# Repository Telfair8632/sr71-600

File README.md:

# SR71-600 — A Twin-Engine 600 mm RC Blackbird

A fully independent engineering project: the complete digital build package, firmware, and verification records for a twin-engine radio-controlled aircraft modeled on the SR-71.

> As a fully independent engineering project, I am designing and building a twin-engine radio-controlled aircraft modeled on the SR-71, with a 590 mm airframe and a 190.7 g mass budget. I completed the full digital design phase myself: a parametric CAD model, an engineering report with assembly documentation, full-scale manufacturing templates, a costed procurement plan, and automated design-verification checks. I then established a staged verification program for the flight controller, a Raspberry Pi Pico 2 microcontroller, progressing through fourteen defined debug levels. My level-three firmware—heartbeat indication, USB logging, and watchdog recovery—passed a 30-minute automated endurance test, and my level-four inertial-measurement firmware validated the MPU-6050 sensor, logging 200 Hz data for ten continuous minutes without a dropped sample. Next, I will construct motor mounts and a thrust-test bench, calibrate weight and balance, and complete ground checks before a supervised first flight. This project demonstrates my capacity for self-directed learning, systematic execution, and safety-conscious engineering practice.

**This repository is the V1.0-P0 digital trial-production release. It is not a flight-certified design.**

## Status Snapshot

| Area | State | Evidence |
|---|---|---|
| Parametric CAD model | Done (P0) | `cad/`, `qa/cad_checks.json` |
| Engineering report & assembly manual | Done | `docs/engineering_report.md` / `.pdf` |
| Manufacturing templates (14 laser-cut DXF, 8 printed STL, 1:1 print sheets) | Done | `cut/`, `print/`, `docs/cutting_templates_1to1.pdf` |
| Circuit design (E1) | Done | `docs/circuit_design.md`, `electronics/` |
| Firmware level 3 — minimal firmware, 30-min soak + watchdog | **PASS** (2026-10-07) | `data/test_records.csv` row PICO0, `firmware/scripts/soak_level3_*.log` |
| Firmware level 4 — MPU-6050 IMU @ 200 Hz, 10-min log | **PASS** (2026-10-13); accelerometer scale error corrected in firmware 2026-11-19 | `data/test_records.csv` row IMU0, `firmware/scripts/imu_10min.csv`, `docs/debug_log_2026-11-19.md` |
| Firmware level 6 — four-channel 50 Hz PWM | Compiled (2026-10-19), artifact verified reproducible; flash + logic-analyser verification pending | `firmware/level6_pwm/`, `docs/debug_log_2026-10-19.md` |
| E1 power-distribution PCB (V1.1) | **Received 2026-11-19, bare board verified by continuity**, assembly pending (3 parts still missing) | `pcb/e1_power_dist_2s/`, `docs/pcb_v1_1_wiring.md` |
| SMD flight-control board V2 | **Designed 2026-11-19**: 65 × 85 mm, 37 SMD parts, routed, DRC 0/0; ordering pending | `pcb/sr71_ctrl_v2/`, `docs/pcb_v2_smd_design.md` |
| Physical build & flight test | In progress — V1.1 becomes the bench board; the V2 SMD board is the flight-intent board | `docs/debug_log_2026-11-19.md`, `ROADMAP.md` |

## Repository Layout

```
cad/                FreeCAD source model (.FCStd) and STEP export
config/             design.json — the parametric design entry point
cut/                14 laser-cutting DXF templates (foam sheets)
print/              8 3D-printed parts (motor saddles, fin saddles, control horns)
docs/               engineering report, assembly instructions, circuit design,
                    staged debug procedure, debug logs, assessments, learning path
electronics/        wiring diagram (SVG) and netlist (CSV), revision E1
pcb/                two boards: e1_power_dist_2s (V1.1, through-hole, received) and
                    sr71_ctrl_v2 (V2, SMD, 65 x 85 mm) — KiCad sources, Gerbers,
                    CPL, BOM, renders
firmware/           Pico 2 (RP2350) firmware: level3_minimal, level4_imu, level6_pwm,
                    bus_doctor, plus the automated acceptance scripts and raw test logs
data/               BOM, procurement budget, test records, measurement records,
                    analysis outputs (JSON) consumed by the generators
src/                Python generators that build the CAD, drawings, PDFs, DXFs,
                    and the offline 3D viewer from config/design.json
qa/                 recorded verification evidence (CAD checks, document checks,
                    viewer checks, run logs)
references/         source links for the reference documents used during design
ROADMAP.md          phase plan, firmware ladder status, next actions, v2 gate
build.ps1           one-command regeneration of the digital package
```

Start here:

- Open `model_preview.html` in a browser — an offline interactive 3D view (drag to rotate; top/side/internal views).
- Read `docs/engineering_report.md` — design, calculations, assembly, wiring, testing, and budget.
- `docs/assembly_dimensions.pdf` and `docs/cutting_templates_1to1.pdf` — dimensioned drawings and 1:1 print templates.
- `docs/debug_procedure.md` — the 14-level staged verification program.
- `docs/debug_log_2026-10-13.md`, `docs/debug_log_2026-10-19.md`, and `docs/log_2026-10-21_e1_pcb.md` — troubleshooting retrospective, board bring-up log, and the PCB design/order log.

## Design Baseline

- Envelope 590 mm long (including propeller thickness), 420 mm span, 190 mm motor axis spacing; belly landing.
- Two micro brushless motors (EX1103 KV11000) driving 2-inch normal/reverse propellers on a 2S battery.
- Mass budget 190.7 g, including a 20 g unallocated reserve and 16 g removable steel ballast; final ballast is set by measured CG.
- First-order CG window from the full chine projection: 292.2–298.6 mm from the nose (not an aerodynamically validated result).
- First-round procurement budget CNY 3420 with CNY 1580 held back for rework and spares; not live pricing.

## Reproducing the Build

Requirements: [FreeCAD 1.1.3](https://www.freecad.org) (its bundled Python 3.11) and a Python 3.12 with `ezdxf`, `shapely`, `reportlab`, `pymupdf` (or a `tools/pydeps` folder next to this repo, which the scripts pick up automatically).

```powershell
powershell -ExecutionPolicy Bypass -File build.ps1
```

The design entry points are `config/design.json` and `src/build_cad.py`. The FCStd spreadsheet is a readable parameter list; not every solid is driven by it in real time. The scripts contain explicit modeling stations — if you change overall proportions, revise them together and re-run all checks. STLs are at local origins; STEP/FCStd use whole-aircraft coordinates. Equipment in the CAD is envelope geometry; the appearance prototype is not a strict scale replica.

Rebuilds preserve the measured columns in `data/bom.csv` and all user records in `data/test_records.csv`.

Firmware rebuild instructions (Pico SDK toolchain): see `firmware/README.md`.

## Safety and Limitations

- This is a **digital trial-production release**: hole positions and flight parameters are not measured-and-released values.
- Blank test records must never be treated as passed; propeller-disc geometry is illustrative, not a manufacturable propeller.
- The parachute bay is reserved space only — there is no parachute recovery system.
- Propellers stay off for debug levels 0–7; powered tests only on a fixed bench, never with people in the propeller plane.
- First flights are conducted by an experienced pilot, at a field with confirmed permission, clearance, and people segregation.

## License

MIT — see `LICENSE`. Third-party reference documents (receiver and motor manuals) used during design are not redistributed in this repository; see `references/sources.json` for their origins.

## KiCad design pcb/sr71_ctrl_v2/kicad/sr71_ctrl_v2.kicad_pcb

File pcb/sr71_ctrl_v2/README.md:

# SR71-600 Flight-Control Board V2 (SMD)

Board: 65 × 85 mm, 2 layers, 1.0 mm, 1 oz copper, 37 SMD parts + 4 × M2 mounting holes.
Designed 2026-11-19; DRC clean (0 violations / 0 unconnected); **not yet ordered**.
Revision 2026-11-20: the four board-outline corner arcs had the wrong sweep direction; fixed in the board file and the fabrication package re-exported.

This board replaces the through-hole `pcb/e1_power_dist_2s/` board as the flight-intent control board. The battery / ESC / UBEC distribution moved off the board, so the board now starts at 5 V and can be assembled by a PCB house in one pass.

- Electrical design and rationale: `docs/pcb_v2_smd_design.md`
- Wiring of the previous board (for reference): `docs/pcb_v1_1_wiring.md`
- Design log: `docs/debug_log_2026-11-19.md`

## Contents

```
kicad/sr71_ctrl_v2.kicad_pcb    routed board (KiCad 10)
kicad/sr71_ctrl_v2.kicad_sch    schematic
kicad/sr71_ctrl_v2.net          netlist
fab/gerbers/                    Gerber + Excellon drill set
fab/assembly/bom_sr71_ctrl_v2.csv        37-line BOM (R17/R18 = DNP)
fab/assembly/sr71_ctrl_v2_positions.csv  pick-and-place (KiCad coordinates, Y negative)
renders/board_preview.png       copper preview (top)
renders/refs_map.png            reference designator map
```

## Fabrication

| Option | Value |
|---|---|
| Layers / thickness / copper | 2 / **1.0 mm** / **1 oz** |
| Surface / mask / silk | HASL / green / white |
| Quantity | 5 |
| Assembly | single-side SMT, 5 boards |
| Not placed | R17, R18 (DNP); J5 XT30 (through-hole, hand-solder 2 pads) |

Estimated cost: CNY 150–250 for five assembled boards, 3–6 days.

## Electrical summary

Same netlist as E1 minus the power section (25 nets):

- J5 = 5 V input (XT30; pin 4 = +5 V, pin 3 = GND) — the only hand-soldered joint
- J6/J7 = servo L/R (signal, +5 V, GND); J8/J9 = ESC signal L/R
- J10 = RP1 receiver (5 V, GND, TX → U2 → GP1, RX ← R1 ← GP0)
- J11 = MPU-6050 (3V3, GND, SDA, SCL, INT) — note the SDA/SCL cross against the GY-521 header
- J12/J13 = Pico 2 sockets (SMD, 2 × 20 pins)
- U1 = SN74AHCT125 (SOIC-14), U2 = SN74LVC1G17 (SOT-23-5), Q1 = MMBT3904 (SOT-23)

## Open items

1. Add LCSC part numbers to the BOM for the assembly order.
2. Confirm CPL orientation (KiCad vs JLC convention) in the uploader preview.
3. Order, assemble, then run the bring-up sequence from `docs/debug_procedure.md` levels 1–2 before inserting the Pico.

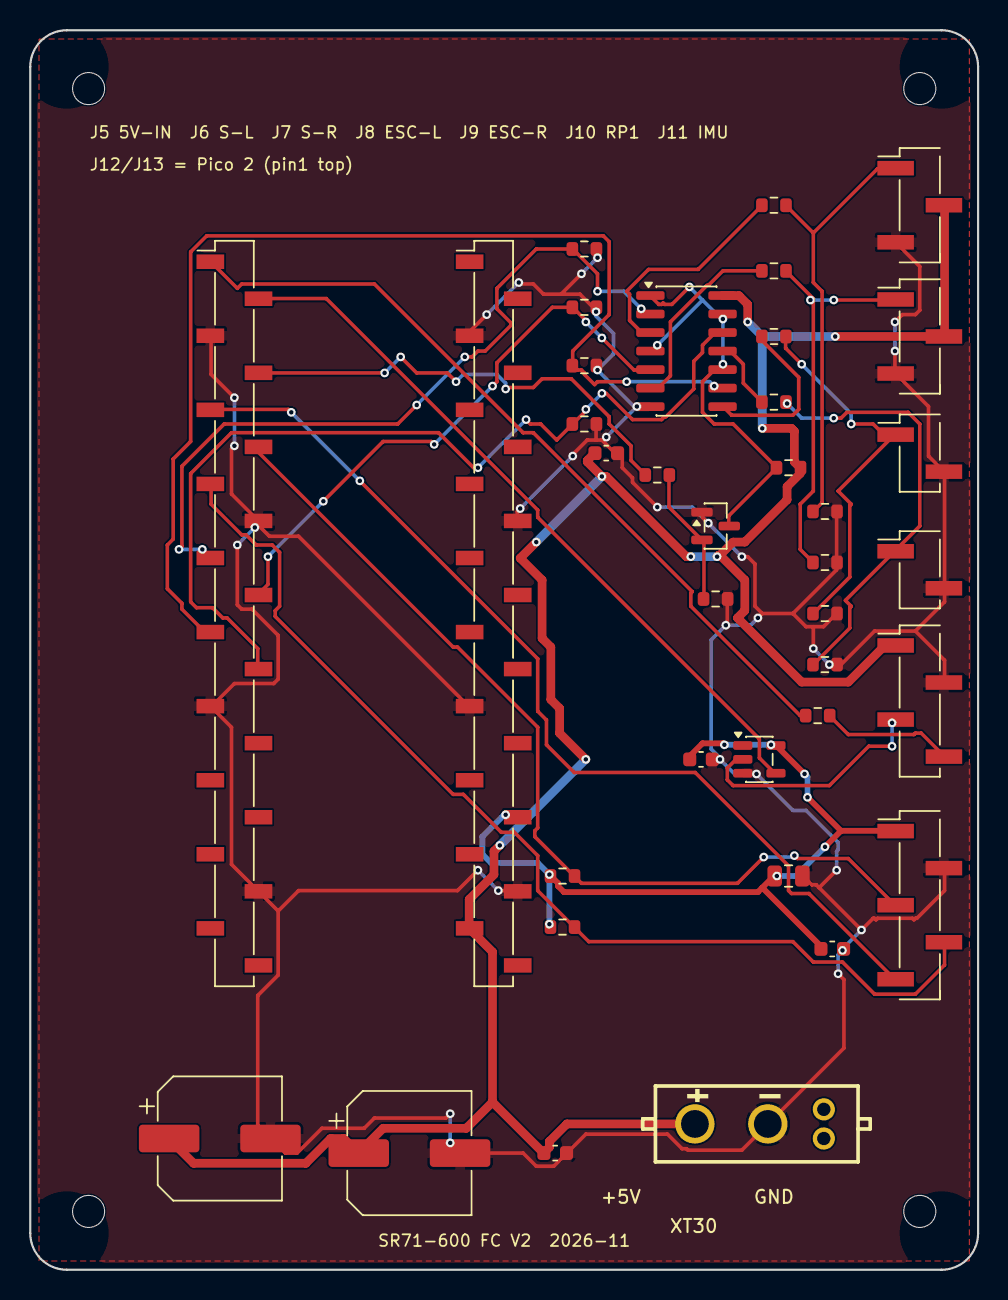
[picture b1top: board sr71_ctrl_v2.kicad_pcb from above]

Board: 2 copper layers, 65.0 x 85.0 mm, 41 parts (0 on the bottom side), 25 nets.

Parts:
C1, C2: 470uF; CP_Elec_8x6.9
C3, C5, C6, C7: 100nF; C_0603_1608Metric
C4: 10uF; C_0805_2012Metric
H: MountingHole_2.2mm_M2
H#2, H#3, H#4: MountingHole_2.2mm_M2
J5: UBEC_5V; CONN-TH_XT30PB-M
J6: S-L; PinHeader_1x03_P2.54mm_Vertical_SMD_Pin1Left
J7: S-R; PinHeader_1x03_P2.54mm_Vertical_SMD_Pin1Left
J8: ESC-L; PinHeader_1x02_P2.54mm_Vertical_SMD_Pin1Left
J9: ESC-R; PinHeader_1x02_P2.54mm_Vertical_SMD_Pin1Left
J10: RP1; PinHeader_1x04_P2.54mm_Vertical_SMD_Pin1Left
J11: IMU; PinHeader_1x05_P2.54mm_Vertical_SMD_Pin1Left
J12: PICO_L; PinSocket_1x20_P2.54mm_Vertical_SMD_Pin1Left
J13: PICO_R; PinSocket_1x20_P2.54mm_Vertical_SMD_Pin1Left
Q1: 2N3904BU; SOT-23
R1: 1k; R_0603_1608Metric
R2, R17, R18: 4k7; R_0603_1608Metric
R3, R4, R5, R6: 220R; R_0603_1608Metric
R7, R8, R9, R10, R11, R12, R13, R14, R15, R16: 10k; R_0603_1608Metric
U1: SN74AHCT125N; SOIC-14_3.9x8.7mm_P1.27mm
U2: SN74LVC1G17DB; SOT-23-5

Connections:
+3V3: C4.1, C5.1, C7.1, J11.1, J13.16, R17.1, R18.1, U2.5
+5V: C1.1, C2.1, C3.1, C6.1, J5.4, J6.2, J7.2, J10.1, J13.19, R11.2, U1.14
ESC_L_PWM: J8.1, R5.2, R9.1
ESC_R_PWM: J9.1, R6.2, R10.1
GND: C1.2, C2.2, C3.2, C4.2, C5.2, C6.2, C7.2, J5.3, J6.3, J7.3, J8.2, J9.2, J10.2, J11.2, J12.3, J12.8, J12.13, J12.18, J13.3, J13.8, J13.13, J13.18, Q1.1, R7.2, R8.2, R9.2, R10.2, R12.2, R13.2, R14.2, R15.2, R16.2, U1.7, U2.3
GP0: J12.1, R1.1
GP1: J12.2, U2.4
GP2: J12.4, R2.1
GP3: J11.5, J12.5
GP6: J12.9, R13.1, U1.2
GP7: J12.10, R14.1, U1.5
GP8: J12.11, R15.1, U1.9
GP9: J12.12, R16.1, U1.12
OE_N: Q1.3, R11.1, U1.1, U1.4, U1.10, U1.13
Q1_B: Q1.2, R2.2, R12.1
RP1_RX: J10.4, R1.2
RP1_TX: J10.3, U2.2
SCL: J11.4, J12.7, R18.2
SDA: J11.3, J12.6, R17.2
SV_L_PWM: J6.1, R3.2, R7.1
SV_R_PWM: J7.1, R4.2, R8.1
U1_1Y: R3.1, U1.3
U1_2Y: R4.1, U1.6
U1_3Y: R5.1, U1.8
U1_4Y: R6.1, U1.11

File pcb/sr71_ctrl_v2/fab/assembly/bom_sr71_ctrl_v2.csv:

Ref,Value,Footprint,Side,DNP
C1,470uF,CP_Elec_8x6.9,top,
C2,470uF,CP_Elec_8x6.9,top,
C3,100nF,C_0603_1608Metric,top,
C4,10uF,C_0805_2012Metric,top,
C5,100nF,C_0603_1608Metric,top,
C6,100nF,C_0603_1608Metric,top,
C7,100nF,C_0603_1608Metric,top,
J5,UBEC_5V,CONN-TH_XT30PB-M,top,
J6,S-L,PinHeader_1x03_P2.54mm_Vertical_SMD_Pin1Left,top,
J7,S-R,PinHeader_1x03_P2.54mm_Vertical_SMD_Pin1Left,top,
J8,ESC-L,PinHeader_1x02_P2.54mm_Vertical_SMD_Pin1Left,top,
J9,ESC-R,PinHeader_1x02_P2.54mm_Vertical_SMD_Pin1Left,top,
J10,RP1,PinHeader_1x04_P2.54mm_Vertical_SMD_Pin1Left,top,
J11,IMU,PinHeader_1x05_P2.54mm_Vertical_SMD_Pin1Left,top,
J12,PICO_L,PinSocket_1x20_P2.54mm_Vertical_SMD_Pin1Left,top,
J13,PICO_R,PinSocket_1x20_P2.54mm_Vertical_SMD_Pin1Left,top,
Q1,2N3904BU,SOT-23,top,
R1,1k,R_0603_1608Metric,top,
R2,4k7,R_0603_1608Metric,top,
R3,220R,R_0603_1608Metric,top,
R4,220R,R_0603_1608Metric,top,
R5,220R,R_0603_1608Metric,top,
R6,220R,R_0603_1608Metric,top,
R7,10k,R_0603_1608Metric,top,
R8,10k,R_0603_1608Metric,top,
R9,10k,R_0603_1608Metric,top,
R10,10k,R_0603_1608Metric,top,
R11,10k,R_0603_1608Metric,top,
R12,10k,R_0603_1608Metric,top,
R13,10k,R_0603_1608Metric,top,
R14,10k,R_0603_1608Metric,top,
R15,10k,R_0603_1608Metric,top,
R16,10k,R_0603_1608Metric,top,
R17,4k7,R_0603_1608Metric,top,DNP
R18,4k7,R_0603_1608Metric,top,DNP
U1,SN74AHCT125N,SOIC-14_3.9x8.7mm_P1.27mm,top,
U2,SN74LVC1G17DB,SOT-23-5,top,
